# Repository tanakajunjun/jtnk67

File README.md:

# jtnk67
custom keyboard

## directory structure
### GL516_JTNK67
- GL516 based template and setting file for design data.
### Inkscape
- Data sheet for laser cutting.
### qmk
- qmk firmware.
### via
- json file for via keyboard.

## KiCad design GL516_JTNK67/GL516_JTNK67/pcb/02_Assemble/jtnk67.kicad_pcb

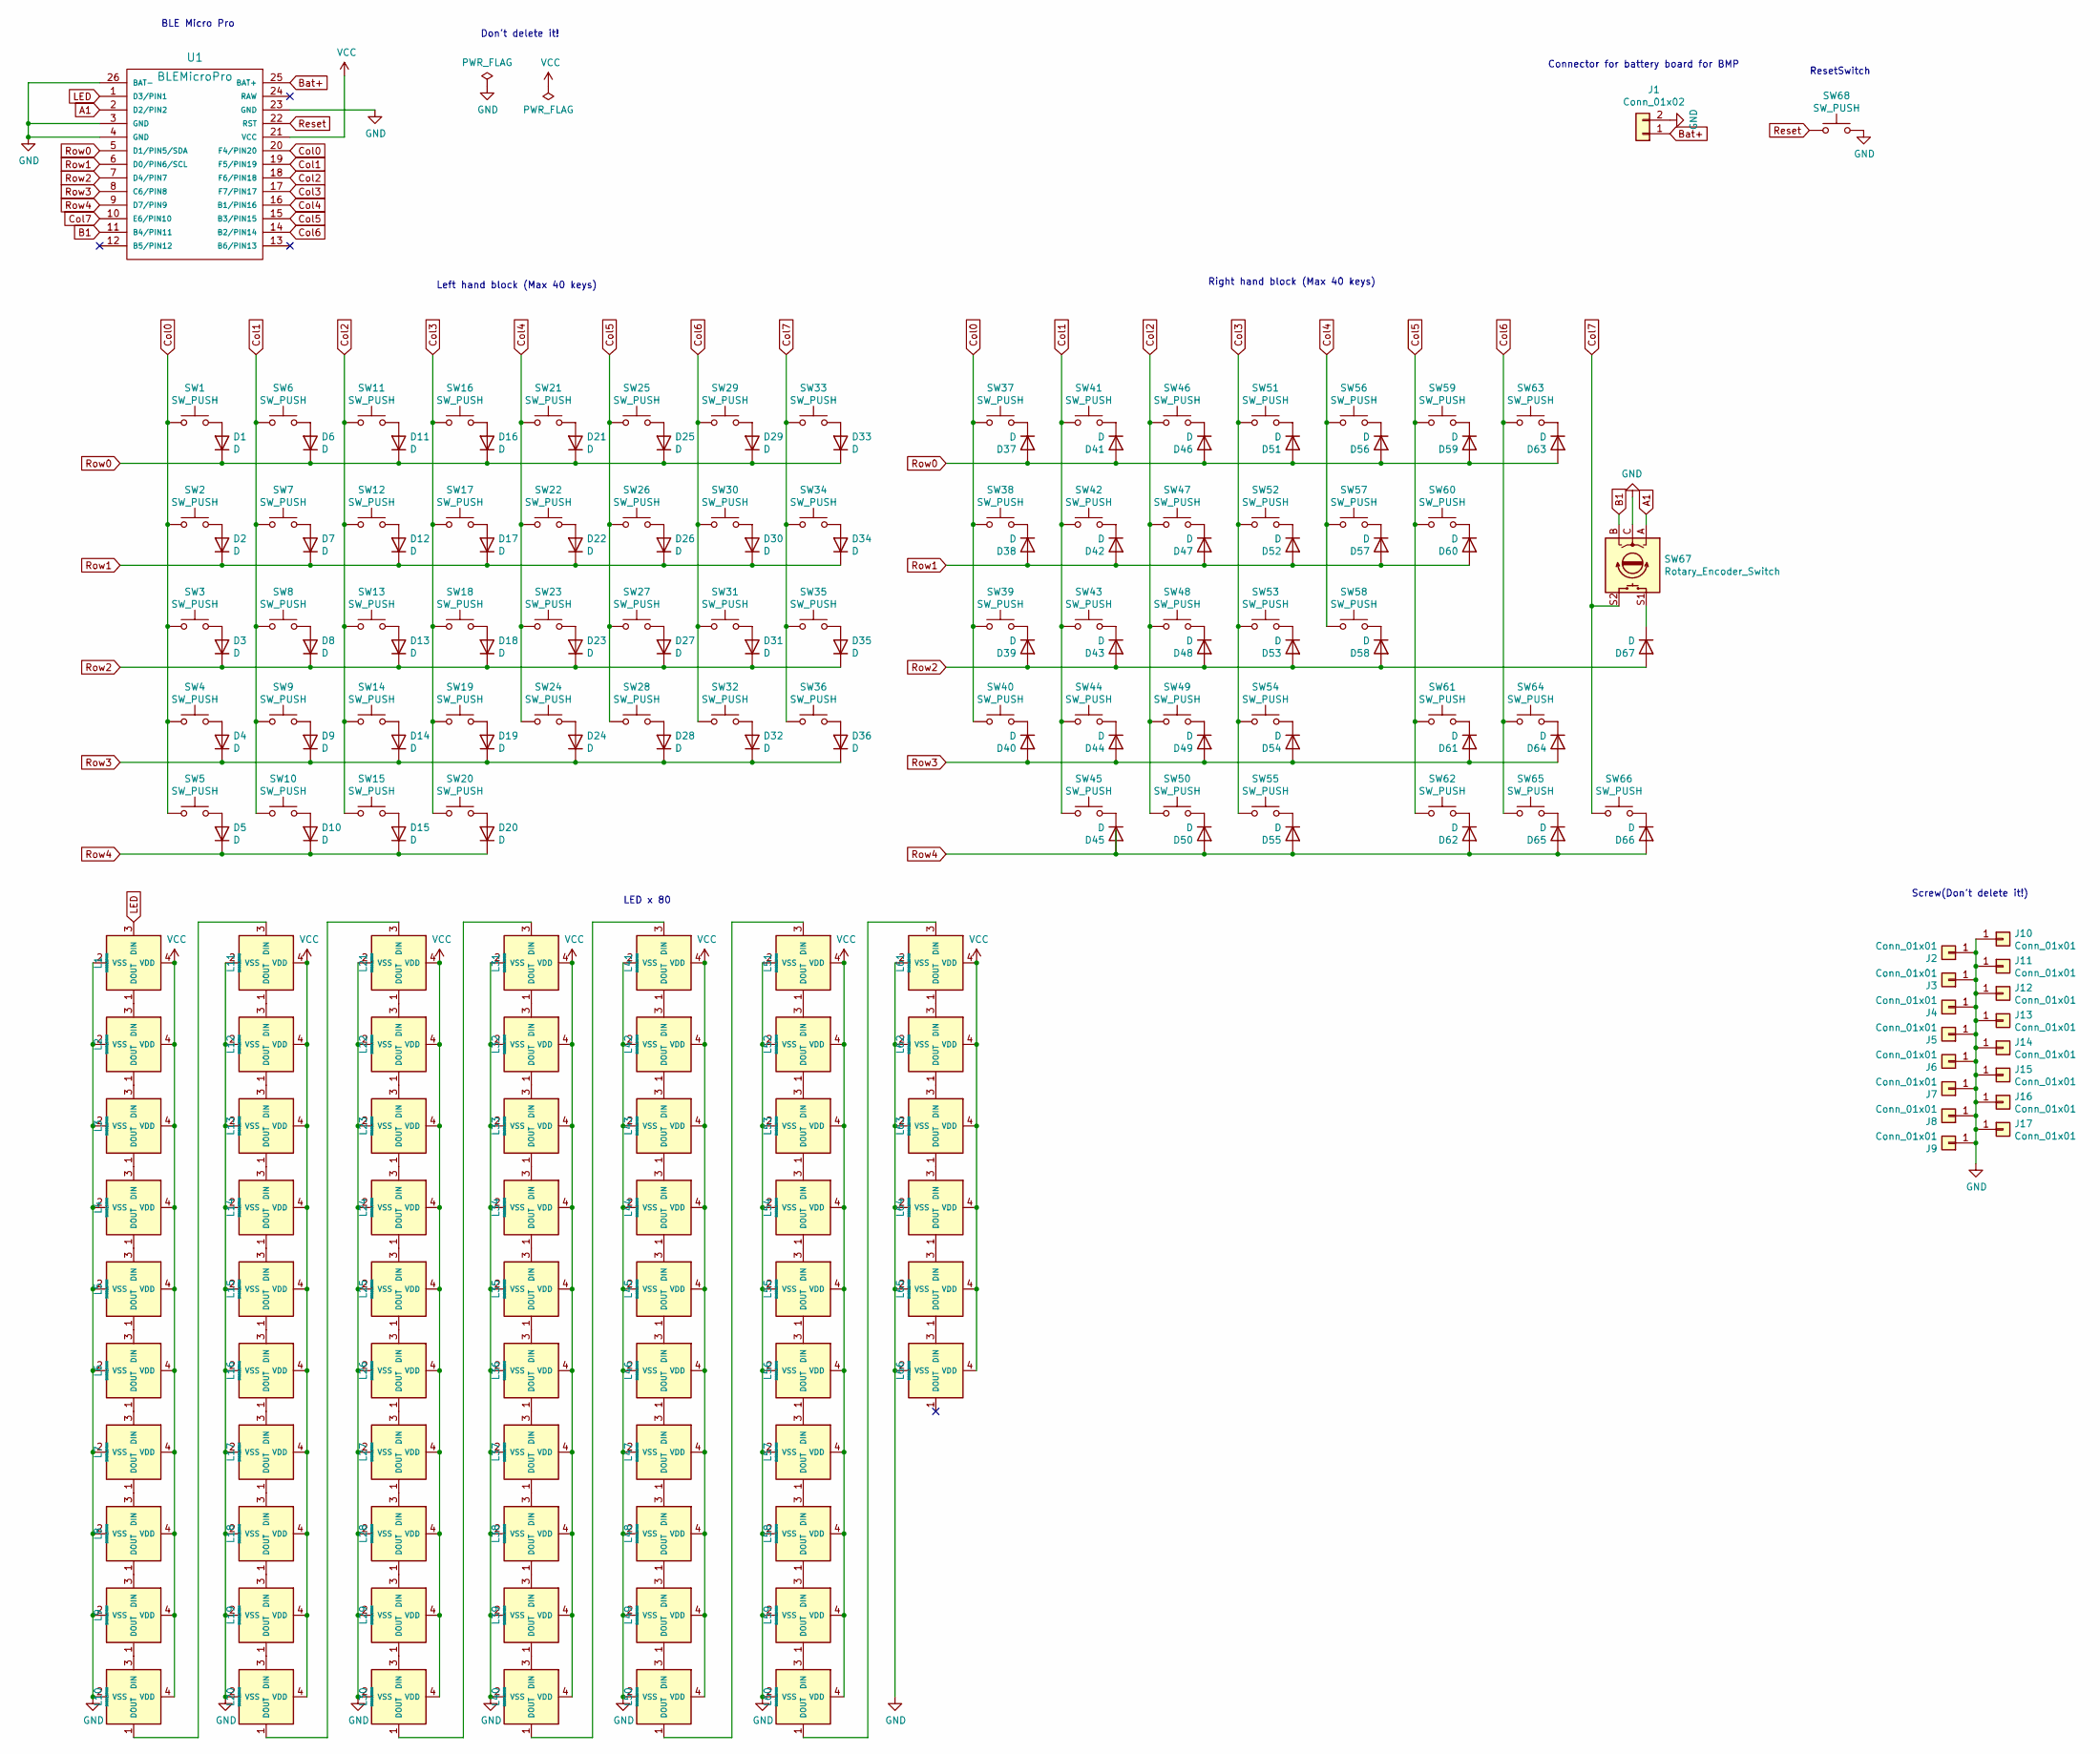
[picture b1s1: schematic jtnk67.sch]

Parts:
D1, D2, D3, D4, D5, D6, D7, D8, D9, D10, D11, D12, D13, D14, D15, D16, D17, D18, D19, D20, D21, D22, D23, D24, D25, D26, D27, D28, D29, D30, D31, D32, D33, D34, D35, D36, D37, D38, D39, D40, D41, D42, D43, D44, D45, D46, D47, D48, D49, D50, D51, D52, D53, D54, D55, D56, D57, D58, D59, D60, D61, D62, D63, D64, D65, D66, D67: D; Diode_TH_SMD
J1: Conn_01x02; Battery_XH2.5_GL_PCB
J2, J3, J4, J5, J6, J7: Conn_01x01; m2_Screw_Hole_EdgeCuts
J8, J9, J10, J11, J12, J13, J14, J15, J16, J17: Conn_01x01; m2_Screw_Hole_Fab
L1, L2, L3, L4, L5, L6, L7, L8, L9, L10, L11, L12, L13, L14, L15, L16, L17, L18, L19, L20, L21, L22, L23, L24, L25, L26, L27, L28, L29, L30, L31, L32, L33, L34, L35, L36, L37, L38, L39, L40, L41, L42, L43, L44, L45, L46, L47, L48, L49, L50, L51, L52, L53, L54, L55, L56, L57, L58, L59, L60, L61, L62, L63, L64, L65, L66: SK6812MINI; LED_SK6812MINI-E_BL
SW1, SW6, SW7, SW8, SW9, SW11, SW12, SW13, SW14, SW16, SW17, SW18, SW19, SW21, SW22, SW23, SW24, SW25, SW26, SW27, SW28, SW29, SW30, SW31, SW32, SW33, SW34, SW35, SW36, SW37, SW38, SW39, SW40, SW41, SW42, SW43, SW44, SW46, SW47, SW48, SW49, SW51, SW52, SW53, SW54, SW56, SW57, SW58, SW59, SW62, SW63, SW64, SW65, SW66: SW_PUSH; CherryMX_Hotswap_1u
SW2: SW_PUSH; CherryMX_Hotswap_1.5u
SW3, SW61: SW_PUSH; CherryMX_Hotswap_1.75u
SW4: SW_PUSH; CherryMX_Hotswap_2.25u
SW5, SW10, SW15, SW45, SW50, SW55: SW_PUSH; CherryMX_Hotswap_1.25u
SW20: SW_PUSH; CherryMX_Hotswap_6.25u
SW60: SW_PUSH; CherryMX_Hotswap_ISO_Rev
SW67: Rotary_Encoder_Switch; RotaryEncoder_EC12E
SW68: SW_PUSH; ResetSW
U1: BLEMicroPro; Micon_BMP_GL

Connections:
A1: SW67.A, U1.2 (D2/PIN2)
B1: SW67.B, U1.11 (B4/PIN11)
Bat+: J1.1, U1.25 (BAT+)
Col0: SW1.1, SW2.1, SW3.1, SW4.1, SW5.1, SW37.1, SW38.1, SW39.1, SW40.1, U1.20 (F4/PIN20)
Col1: SW6.1, SW7.1, SW8.1, SW9.1, SW10.1, SW41.1, SW42.1, SW43.1, SW44.1, SW45.1, U1.19 (F5/PIN19)
Col2: SW11.1, SW12.1, SW13.1, SW14.1, SW15.1, SW46.1, SW47.1, SW48.1, SW49.1, SW50.1, U1.18 (F6/PIN18)
Col3: SW16.1, SW17.1, SW18.1, SW19.1, SW20.1, SW51.1, SW52.1, SW53.1, SW54.1, SW55.1, U1.17 (F7/PIN17)
Col4: SW21.1, SW22.1, SW23.1, SW24.1, SW56.1, SW57.1, SW58.1, U1.16 (B1/PIN16)
Col5: SW25.1, SW26.1, SW27.1, SW28.1, SW59.1, SW60.1, SW61.1, SW62.1, U1.15 (B3/PIN15)
Col6: SW29.1, SW30.1, SW31.1, SW32.1, SW63.1, SW64.1, SW65.1, U1.14 (B2/PIN14)
Col7: SW33.1, SW34.1, SW35.1, SW36.1, SW66.1, SW67.S2, U1.10 (E6/PIN10)
GND: J1.2, J2.1, J3.1, J4.1, J5.1, J6.1, J7.1, J8.1, J9.1, J10.1, J11.1, J12.1, J13.1, J14.1, J15.1, J16.1, J17.1, L1.2 (VSS), L2.2 (VSS), L3.2 (VSS), L4.2 (VSS), L5.2 (VSS), L6.2 (VSS), L7.2 (VSS), L8.2 (VSS), L9.2 (VSS), L10.2 (VSS), L11.2 (VSS), L12.2 (VSS), L13.2 (VSS), L14.2 (VSS), L15.2 (VSS), L16.2 (VSS), L17.2 (VSS), L18.2 (VSS), L19.2 (VSS), L20.2 (VSS), L21.2 (VSS), L22.2 (VSS), L23.2 (VSS), L24.2 (VSS), L25.2 (VSS), L26.2 (VSS), L27.2 (VSS), L28.2 (VSS), L29.2 (VSS), L30.2 (VSS), L31.2 (VSS), L32.2 (VSS), L33.2 (VSS), L34.2 (VSS), L35.2 (VSS), L36.2 (VSS), L37.2 (VSS), L38.2 (VSS), L39.2 (VSS), L40.2 (VSS), L41.2 (VSS), L42.2 (VSS), L43.2 (VSS), L44.2 (VSS), L45.2 (VSS), L46.2 (VSS), L47.2 (VSS), L48.2 (VSS), L49.2 (VSS), L50.2 (VSS), L51.2 (VSS), L52.2 (VSS), L53.2 (VSS), L54.2 (VSS), L55.2 (VSS), L56.2 (VSS), L57.2 (VSS), L58.2 (VSS), L59.2 (VSS), L60.2 (VSS), L61.2 (VSS), L62.2 (VSS), L63.2 (VSS), L64.2 (VSS), L65.2 (VSS), L66.2 (VSS), SW67.C, SW68.2, U1.3 (GND), U1.4 (GND), U1.23 (GND), U1.26 (BAT-)
LED: L1.3 (DIN), U1.1 (D3/PIN1)
unnamed: D1.2 (A), SW1.2
unnamed: D2.2 (A), SW2.2
unnamed: D3.2 (A), SW3.2
unnamed: D4.2 (A), SW4.2
unnamed: D5.2 (A), SW5.2
unnamed: D6.2 (A), SW6.2
unnamed: D7.2 (A), SW7.2
unnamed: D8.2 (A), SW8.2
unnamed: D9.2 (A), SW9.2
unnamed: D10.2 (A), SW10.2
unnamed: D11.2 (A), SW11.2
unnamed: D12.2 (A), SW12.2
unnamed: D13.2 (A), SW13.2
unnamed: D14.2 (A), SW14.2
unnamed: D15.2 (A), SW15.2
unnamed: D16.2 (A), SW16.2
unnamed: D17.2 (A), SW17.2
unnamed: D18.2 (A), SW18.2
unnamed: D19.2 (A), SW19.2
unnamed: D20.2 (A), SW20.2
unnamed: D21.2 (A), SW21.2
unnamed: D22.2 (A), SW22.2
unnamed: D23.2 (A), SW23.2
unnamed: D24.2 (A), SW24.2
unnamed: D25.2 (A), SW25.2
unnamed: D26.2 (A), SW26.2
unnamed: D27.2 (A), SW27.2
unnamed: D28.2 (A), SW28.2
unnamed: D29.2 (A), SW29.2
unnamed: D30.2 (A), SW30.2
unnamed: D31.2 (A), SW31.2
unnamed: D32.2 (A), SW32.2
unnamed: D33.2 (A), SW33.2
unnamed: D34.2 (A), SW34.2
unnamed: D35.2 (A), SW35.2
unnamed: D36.2 (A), SW36.2
unnamed: D37.1 (K), SW37.2
unnamed: D38.1 (K), SW38.2
unnamed: D39.1 (K), SW39.2
unnamed: D40.1 (K), SW40.2
unnamed: D41.1 (K), SW41.2
unnamed: D42.1 (K), SW42.2
unnamed: D43.1 (K), SW43.2
unnamed: D44.1 (K), SW44.2
unnamed: D45.1 (K), SW45.2
unnamed: D46.1 (K), SW46.2
unnamed: D47.1 (K), SW47.2
unnamed: D48.1 (K), SW48.2
unnamed: D49.1 (K), SW49.2
unnamed: D50.1 (K), SW50.2
unnamed: D51.1 (K), SW51.2
unnamed: D52.1 (K), SW52.2
unnamed: D53.1 (K), SW53.2
unnamed: D54.1 (K), SW54.2
unnamed: D55.1 (K), SW55.2
unnamed: D56.1 (K), SW56.2
unnamed: D57.1 (K), SW57.2
unnamed: D58.1 (K), SW58.2
unnamed: D59.1 (K), SW59.2
unnamed: D60.1 (K), SW60.2
unnamed: D61.1 (K), SW61.2
unnamed: D62.1 (K), SW62.2
unnamed: D63.1 (K), SW63.2
unnamed: D64.1 (K), SW64.2
unnamed: D65.1 (K), SW65.2
unnamed: D66.1 (K), SW66.2
unnamed: D67.1 (K), SW67.S1
unnamed: L1.1 (DOUT), L2.3 (DIN)
unnamed: L2.1 (DOUT), L3.3 (DIN)
unnamed: L3.1 (DOUT), L4.3 (DIN)
unnamed: L4.1 (DOUT), L5.3 (DIN)
unnamed: L5.1 (DOUT), L6.3 (DIN)
unnamed: L6.1 (DOUT), L7.3 (DIN)
unnamed: L7.1 (DOUT), L8.3 (DIN)
unnamed: L8.1 (DOUT), L9.3 (DIN)
unnamed: L10.1 (DOUT), L11.3 (DIN)
unnamed: L9.1 (DOUT), L10.3 (DIN)
unnamed: L11.1 (DOUT), L12.3 (DIN)
unnamed: L12.1 (DOUT), L13.3 (DIN)
unnamed: L13.1 (DOUT), L14.3 (DIN)
unnamed: L14.1 (DOUT), L15.3 (DIN)
unnamed: L15.1 (DOUT), L16.3 (DIN)
unnamed: L16.1 (DOUT), L17.3 (DIN)
unnamed: L17.1 (DOUT), L18.3 (DIN)
unnamed: L18.1 (DOUT), L19.3 (DIN)
unnamed: L19.1 (DOUT), L20.3 (DIN)
unnamed: L20.1 (DOUT), L21.3 (DIN)
unnamed: L21.1 (DOUT), L22.3 (DIN)
unnamed: L22.1 (DOUT), L23.3 (DIN)
unnamed: L23.1 (DOUT), L24.3 (DIN)
unnamed: L24.1 (DOUT), L25.3 (DIN)
unnamed: L25.1 (DOUT), L26.3 (DIN)
unnamed: L26.1 (DOUT), L27.3 (DIN)
unnamed: L27.1 (DOUT), L28.3 (DIN)
unnamed: L28.1 (DOUT), L29.3 (DIN)
unnamed: L29.1 (DOUT), L30.3 (DIN)
unnamed: L30.1 (DOUT), L31.3 (DIN)
unnamed: L31.1 (DOUT), L32.3 (DIN)
unnamed: L32.1 (DOUT), L33.3 (DIN)
unnamed: L33.1 (DOUT), L34.3 (DIN)
unnamed: L34.1 (DOUT), L35.3 (DIN)
unnamed: L35.1 (DOUT), L36.3 (DIN)
unnamed: L36.1 (DOUT), L37.3 (DIN)
unnamed: L37.1 (DOUT), L38.3 (DIN)
unnamed: L38.1 (DOUT), L39.3 (DIN)
unnamed: L39.1 (DOUT), L40.3 (DIN)
unnamed: L40.1 (DOUT), L41.3 (DIN)
unnamed: L41.1 (DOUT), L42.3 (DIN)
unnamed: L42.1 (DOUT), L43.3 (DIN)
unnamed: L43.1 (DOUT), L44.3 (DIN)
unnamed: L44.1 (DOUT), L45.3 (DIN)
unnamed: L45.1 (DOUT), L46.3 (DIN)
unnamed: L46.1 (DOUT), L47.3 (DIN)
unnamed: L47.1 (DOUT), L48.3 (DIN)
unnamed: L48.1 (DOUT), L49.3 (DIN)
unnamed: L49.1 (DOUT), L50.3 (DIN)
unnamed: L50.1 (DOUT), L51.3 (DIN)
unnamed: L51.1 (DOUT), L52.3 (DIN)
unnamed: L52.1 (DOUT), L53.3 (DIN)
unnamed: L53.1 (DOUT), L54.3 (DIN)
unnamed: L54.1 (DOUT), L55.3 (DIN)
unnamed: L55.1 (DOUT), L56.3 (DIN)
unnamed: L56.1 (DOUT), L57.3 (DIN)
unnamed: L57.1 (DOUT), L58.3 (DIN)
unnamed: L58.1 (DOUT), L59.3 (DIN)
unnamed: L59.1 (DOUT), L60.3 (DIN)
unnamed: L60.1 (DOUT), L61.3 (DIN)
unnamed: L61.1 (DOUT), L62.3 (DIN)
unnamed: L62.1 (DOUT), L63.3 (DIN)
unnamed: L63.1 (DOUT), L64.3 (DIN)
unnamed: L64.1 (DOUT), L65.3 (DIN)
unnamed: L65.1 (DOUT), L66.3 (DIN)
Reset: SW68.1, U1.22 (RST)
Row0: D1.1 (K), D6.1 (K), D11.1 (K), D16.1 (K), D21.1 (K), D25.1 (K), D29.1 (K), D33.1 (K), D37.2 (A), D41.2 (A), D46.2 (A), D51.2 (A), D56.2 (A), D59.2 (A), D63.2 (A), U1.5 (D1/PIN5/SDA)
Row1: D2.1 (K), D7.1 (K), D12.1 (K), D17.1 (K), D22.1 (K), D26.1 (K), D30.1 (K), D34.1 (K), D38.2 (A), D42.2 (A), D47.2 (A), D52.2 (A), D57.2 (A), D60.2 (A), U1.6 (D0/PIN6/SCL)
Row2: D3.1 (K), D8.1 (K), D13.1 (K), D18.1 (K), D23.1 (K), D27.1 (K), D31.1 (K), D35.1 (K), D39.2 (A), D43.2 (A), D48.2 (A), D53.2 (A), D58.2 (A), D67.2 (A), U1.7 (D4/PIN7)
Row3: D4.1 (K), D9.1 (K), D14.1 (K), D19.1 (K), D24.1 (K), D28.1 (K), D32.1 (K), D36.1 (K), D40.2 (A), D44.2 (A), D49.2 (A), D54.2 (A), D61.2 (A), D64.2 (A), U1.8 (C6/PIN8)
Row4: D5.1 (K), D10.1 (K), D15.1 (K), D20.1 (K), D45.2 (A), D50.2 (A), D55.2 (A), D62.2 (A), D65.2 (A), D66.2 (A), U1.9 (D7/PIN9)
VCC: L1.4 (VDD), L2.4 (VDD), L3.4 (VDD), L4.4 (VDD), L5.4 (VDD), L6.4 (VDD), L7.4 (VDD), L8.4 (VDD), L9.4 (VDD), L10.4 (VDD), L11.4 (VDD), L12.4 (VDD), L13.4 (VDD), L14.4 (VDD), L15.4 (VDD), L16.4 (VDD), L17.4 (VDD), L18.4 (VDD), L19.4 (VDD), L20.4 (VDD), L21.4 (VDD), L22.4 (VDD), L23.4 (VDD), L24.4 (VDD), L25.4 (VDD), L26.4 (VDD), L27.4 (VDD), L28.4 (VDD), L29.4 (VDD), L30.4 (VDD), L31.4 (VDD), L32.4 (VDD), L33.4 (VDD), L34.4 (VDD), L35.4 (VDD), L36.4 (VDD), L37.4 (VDD), L38.4 (VDD), L39.4 (VDD), L40.4 (VDD), L41.4 (VDD), L42.4 (VDD), L43.4 (VDD), L44.4 (VDD), L45.4 (VDD), L46.4 (VDD), L47.4 (VDD), L48.4 (VDD), L49.4 (VDD), L50.4 (VDD), L51.4 (VDD), L52.4 (VDD), L53.4 (VDD), L54.4 (VDD), L55.4 (VDD), L56.4 (VDD), L57.4 (VDD), L58.4 (VDD), L59.4 (VDD), L60.4 (VDD), L61.4 (VDD), L62.4 (VDD), L63.4 (VDD), L64.4 (VDD), L65.4 (VDD), L66.4 (VDD), U1.21 (VCC)

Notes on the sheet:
ResetSwitch
Screw(Don't delete it!)
Don't delete it!
BLE Micro Pro
LED x 80
Connector for battery board for BMP
Right hand block (Max 40 keys)
Left hand block (Max 40 keys)

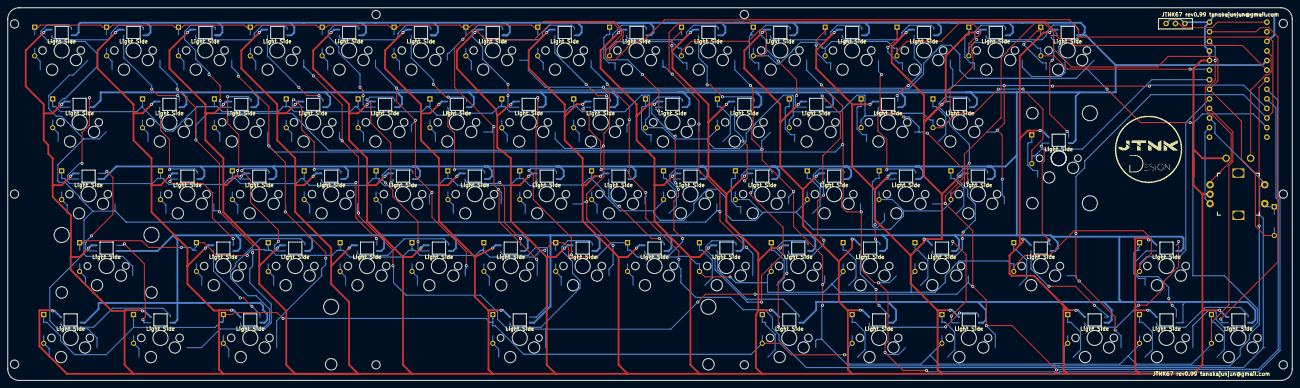
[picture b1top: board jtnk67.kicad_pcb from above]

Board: 2 copper layers, 340.5 x 98.8 mm, 213 parts (0 on the bottom side), 152 nets.

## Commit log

2023-03-08 initial commit
    initial commit.
2023-03-08 modify RGB MATRIX
2023-12-28 support new f/w
